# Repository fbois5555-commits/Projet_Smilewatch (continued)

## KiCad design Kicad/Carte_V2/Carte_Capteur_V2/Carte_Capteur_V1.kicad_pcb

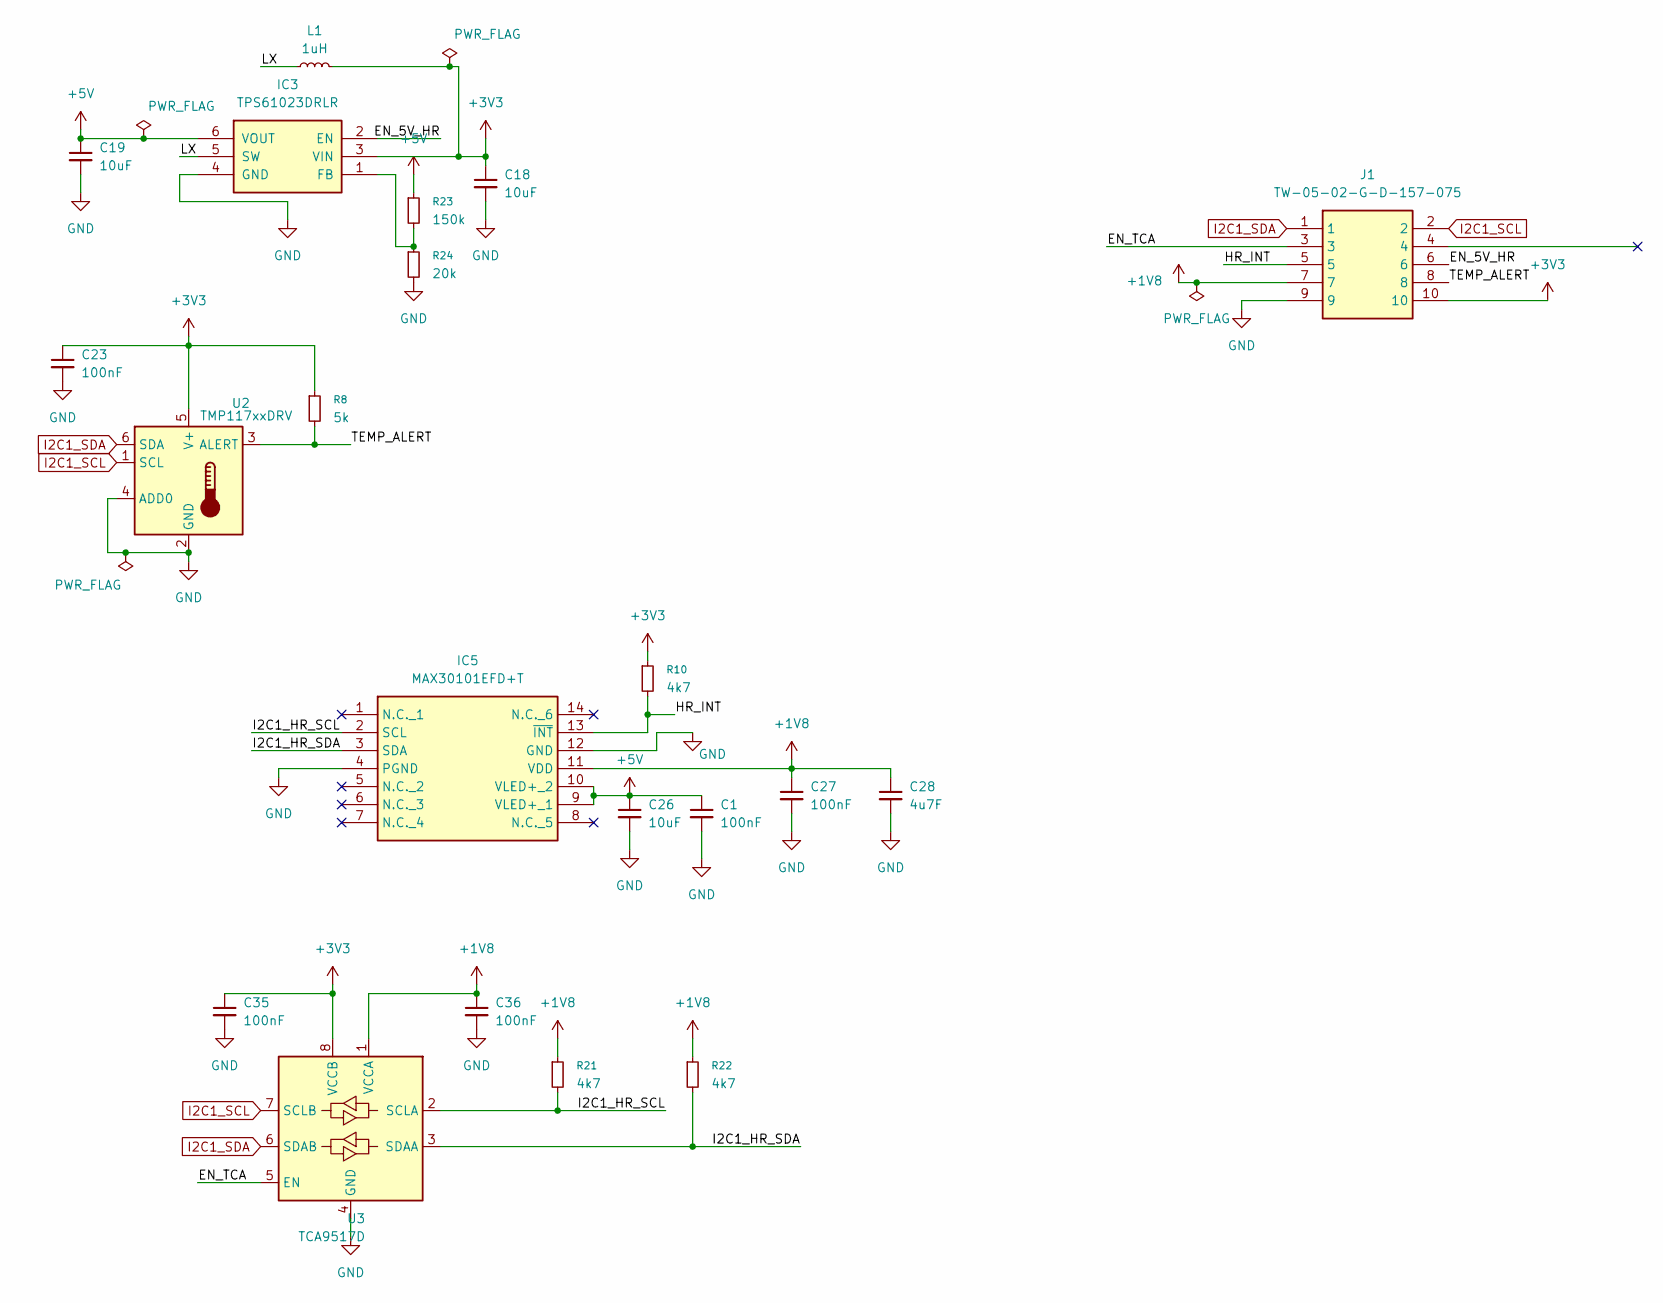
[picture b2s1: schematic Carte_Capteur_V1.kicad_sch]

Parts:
C1, C23, C27, C35, C36: 100nF; C_0402_1005Metric; JLCPCB Part# C1525
C18, C19, C26: 10uF; C_0603_1608Metric; JLCPCB Part# C96446
C28: 4u7F; C_0603_1608Metric; JLCPCB Part# C19666
IC3: TPS61023DRLR; SOT-563; JLCPCB Part# C919459
IC5: MAX30101EFD+T; 14-LEAD-OESIP; Mouser Part Number 700-MAX30101EFD+T
J1: TW-05-02-G-D-157-075; HDRV10W51P200_2X5_1000X400X769P; Mouser Part Number 200-TW0502GD157075
L1: 1uH; L_0603_1608Metric; JLCPCB Part# C882989
R8: 5k; R_0402_1005Metric; JLCPCB Part# C477765
R10, R21, R22: 4k7; R_0402_1005Metric; JLCPCB Part# C25900
R23: 150k; R_0402_1005Metric; JLCPCB Part# C25755
R24: 20k; R_0402_1005Metric; JLCPCB Part# C25765
U2: TMP117xxDRV; WSON-6-1EP_2x2mm_P0.65mm_EP1x1.6mm; JLCPCB Part# C699536
U3: TCA9517D; SOIC-8_3.9x4.9mm_P1.27mm; JLCPCB Part# C182421

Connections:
+1V8: C27.1, C28.1, C36.1, IC5.11 (VDD), J1.7, R21.1, R22.1, U3.1 (VCCA)
+3V3: C18.1, C23.1, C35.1, IC3.3 (VIN), J1.10, L1.2, R8.1, R10.1, U2.5 (V+), U3.8 (VCCB)
+5V: C1.1, C19.1, C26.1, IC3.6 (VOUT), IC5.9 (VLED+_1), IC5.10 (VLED+_2), R23.1
/EN_5V_HR: IC3.2 (EN), J1.6
/EN_TCA: J1.3, U3.5 (EN)
/HR_INT: IC5.13 (~INT), J1.5, R10.2
/I2C1_HR_SCL: IC5.2 (SCL), R21.2, U3.2 (SCLA)
/I2C1_HR_SDA: IC5.3 (SDA), R22.2, U3.3 (SDAA)
/LX: IC3.5 (SW), L1.1
/TEMP_ALERT: J1.8, R8.2, U2.3 (ALERT)
GND: C1.2, C18.2, C19.2, C23.2, C26.2, C27.2, C28.2, C35.2, C36.2, IC3.4 (GND), IC5.4 (PGND), IC5.12 (GND), J1.9, R24.2, U2.2 (GND), U2.4 (ADD0), U3.4 (GND)
I2C1_SCL: J1.2, U2.1 (SCL), U3.7 (SCLB)
I2C1_SDA: J1.1, U2.6 (SDA), U3.6 (SDAB)
unnamed: IC3.1 (FB), R23.2, R24.1

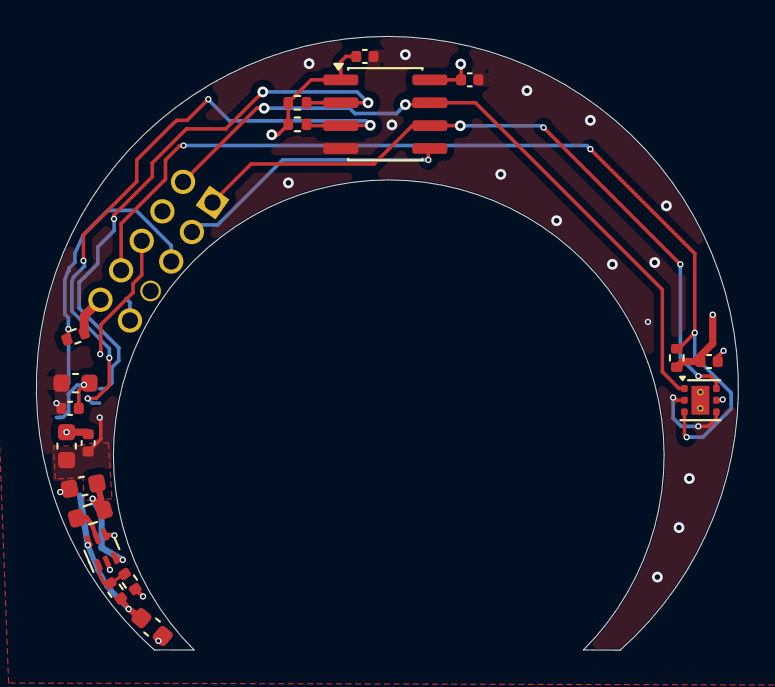
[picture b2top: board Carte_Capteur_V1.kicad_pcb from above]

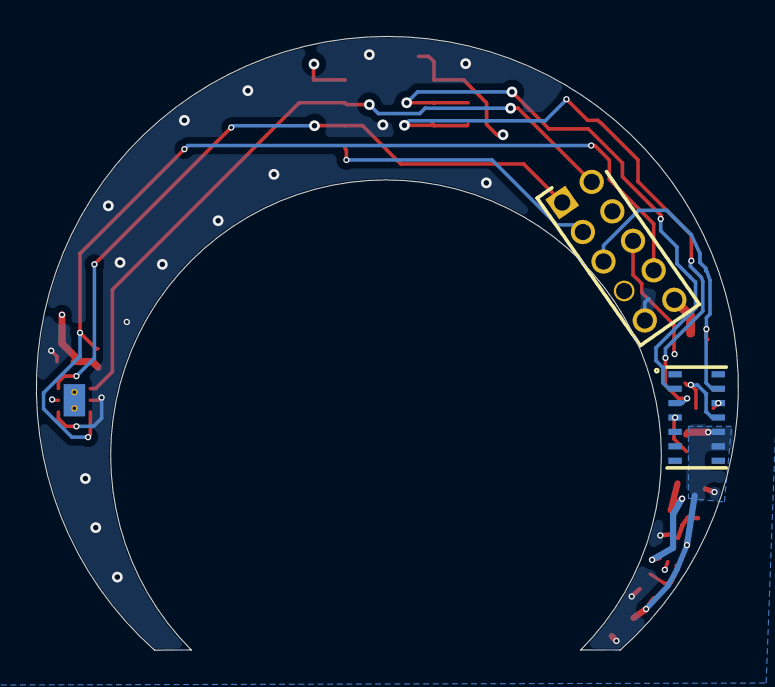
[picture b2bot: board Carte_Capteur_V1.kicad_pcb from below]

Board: 4 copper layers, 39.0 x 34.1 mm, 21 parts (2 on the bottom side), 14 nets.

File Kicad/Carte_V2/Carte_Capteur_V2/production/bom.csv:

Designator,Footprint,Quantity,Value,LCSC Part #
"C1, C23, C27, C35, C36",0402,5,100nF,C1525
"C18, C19, C26",0603,3,10uF,C96446
C28,0603,1,4u7F,C19666
IC3,SOT-563,1,TPS61023DRLR,C919459
IC5,14-LEAD-OESIP,1,MAX30101EFD+T,C2859066
J1,HDRV10W51P200_2X5_1000X400X769P,1,TW-05-02-G-D-157-075,
L1,0603,1,1uH,C882989
"R10, R21, R22",0402,3,4k7,C25900
R23,0402,1,150k,C25755
R24,0402,1,20k,C25765
R8,0402,1,5k,C477765
U2,WSON-6-1EP_2x2mm_P0.65mm_EP1x1.6mm,1,TMP117xxDRV,C699536
U3,SOIC-8_3.9x4.9mm_P1.27mm,1,TCA9517D,C182421

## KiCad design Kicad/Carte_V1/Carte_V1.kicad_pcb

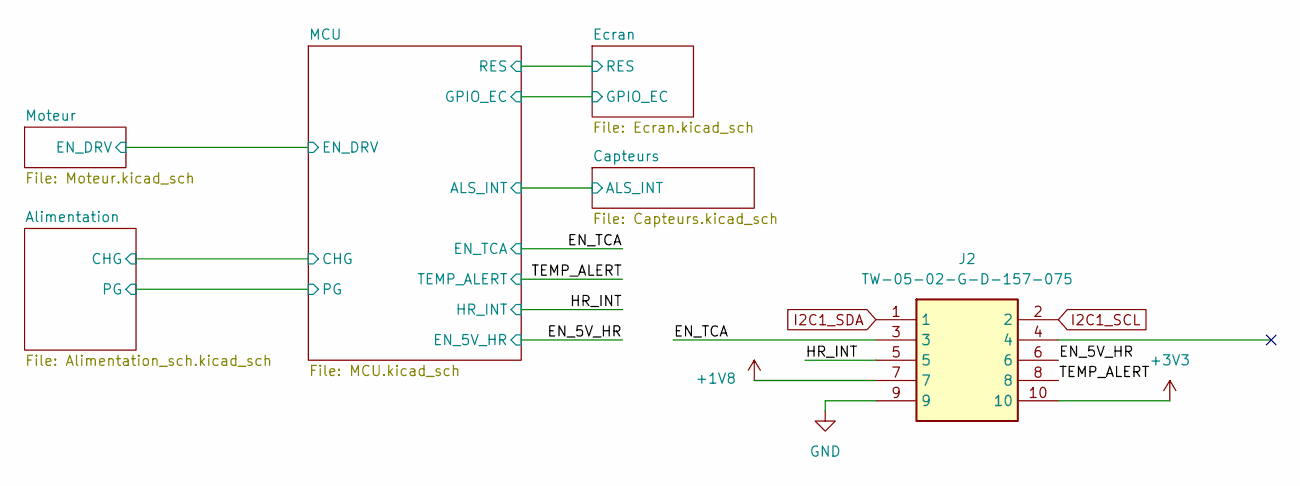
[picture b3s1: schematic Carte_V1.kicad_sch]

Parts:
J2: TW-05-02-G-D-157-075; HDRV10W51P200_2X5_1000X400X769P; Mouser Part Number 200-TW0502GD157075

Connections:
+1V8: J2.7; also elsewhere on the board
+3V3: J2.10; also elsewhere on the board
/EN_5V_HR: J2.6; also elsewhere on the board
/EN_TCA: J2.3; also elsewhere on the board
/HR_INT: J2.5; also elsewhere on the board
/TEMP_ALERT: J2.8; also elsewhere on the board
GND: J2.9; also elsewhere on the board
I2C1_SCL: J2.2; also elsewhere on the board
I2C1_SDA: J2.1; also elsewhere on the board

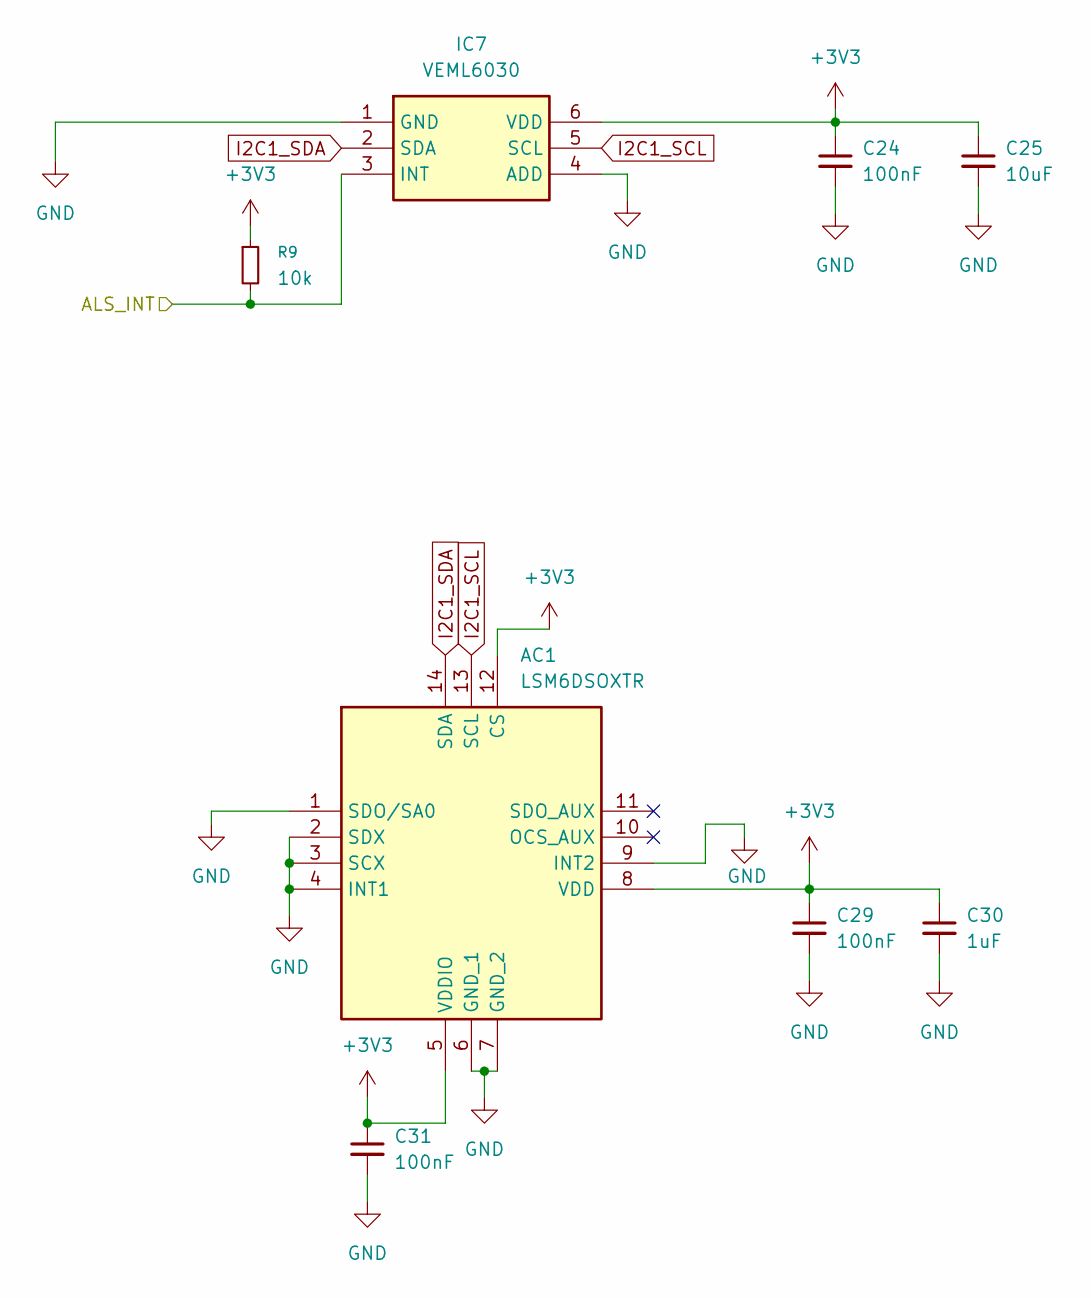
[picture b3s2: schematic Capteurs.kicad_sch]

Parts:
AC1: LSM6DSOXTR; LGA-14_1; Mouser Part Number 511-LSM6DSOXTR
C24, C29, C31: 100nF; C_0402_1005Metric
C25: 10uF; C_0603_1608Metric
C30: 1uF; C_0603_1608Metric
IC7: VEML6030; Mouser Part Number 78-VEML6030
R9: 10k; R_0402_1005Metric

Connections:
+3V3: AC1.5 (VDDIO), AC1.8 (VDD), AC1.12 (CS), C24.1, C25.1, C29.1, C30.1, C31.1, IC7.6 (VDD), R9.1; also elsewhere on the board
/Capteurs/ALS_INT: IC7.3 (INT), R9.2; also elsewhere on the board
GND: AC1.1 (SDO/SA0), AC1.2 (SDX), AC1.3 (SCX), AC1.4 (INT1), AC1.6 (GND_1), AC1.7 (GND_2), AC1.9 (INT2), C24.2, C25.2, C29.2, C30.2, C31.2, IC7.1 (GND), IC7.4 (ADD); also elsewhere on the board
I2C1_SCL: AC1.13 (SCL), IC7.5 (SCL); also elsewhere on the board
I2C1_SDA: AC1.14 (SDA), IC7.2 (SDA); also elsewhere on the board

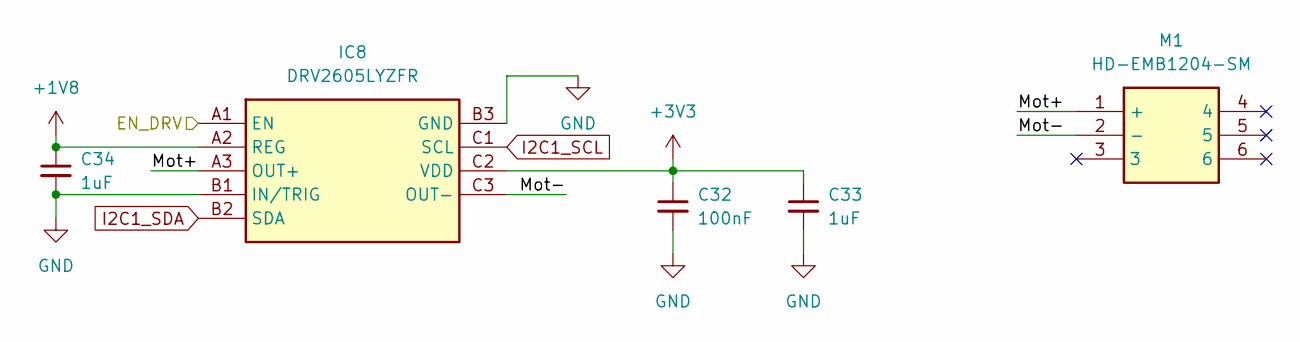
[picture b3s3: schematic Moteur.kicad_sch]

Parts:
C32: 100nF; C_0402_1005Metric
C33, C34: 1uF; C_0603_1608Metric
IC8: DRV2605LYZFR; BGA9C50P3X3_144X144X62; Mouser Part Number 595-DRV2605LYZFR
M1: HD-EMB1204-SM; HDEMB1204SM; Mouser Part Number 665-HD-EMB1204-SM

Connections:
+1V8: C34.1, IC8.A2 (REG); also elsewhere on the board
+3V3: C32.1, C33.1, IC8.C2 (VDD); also elsewhere on the board
/MCU/EN_DRV: IC8.A1 (EN); also elsewhere on the board
/Moteur/Mot+: IC8.A3 (OUT+), M1.1 (+)
/Moteur/Mot-: IC8.C3 (OUT-), M1.2 (-)
GND: C32.2, C33.2, C34.2, IC8.B1 (IN/TRIG), IC8.B3 (GND); also elsewhere on the board
I2C1_SCL: IC8.C1 (SCL); also elsewhere on the board
I2C1_SDA: IC8.B2 (SDA); also elsewhere on the board

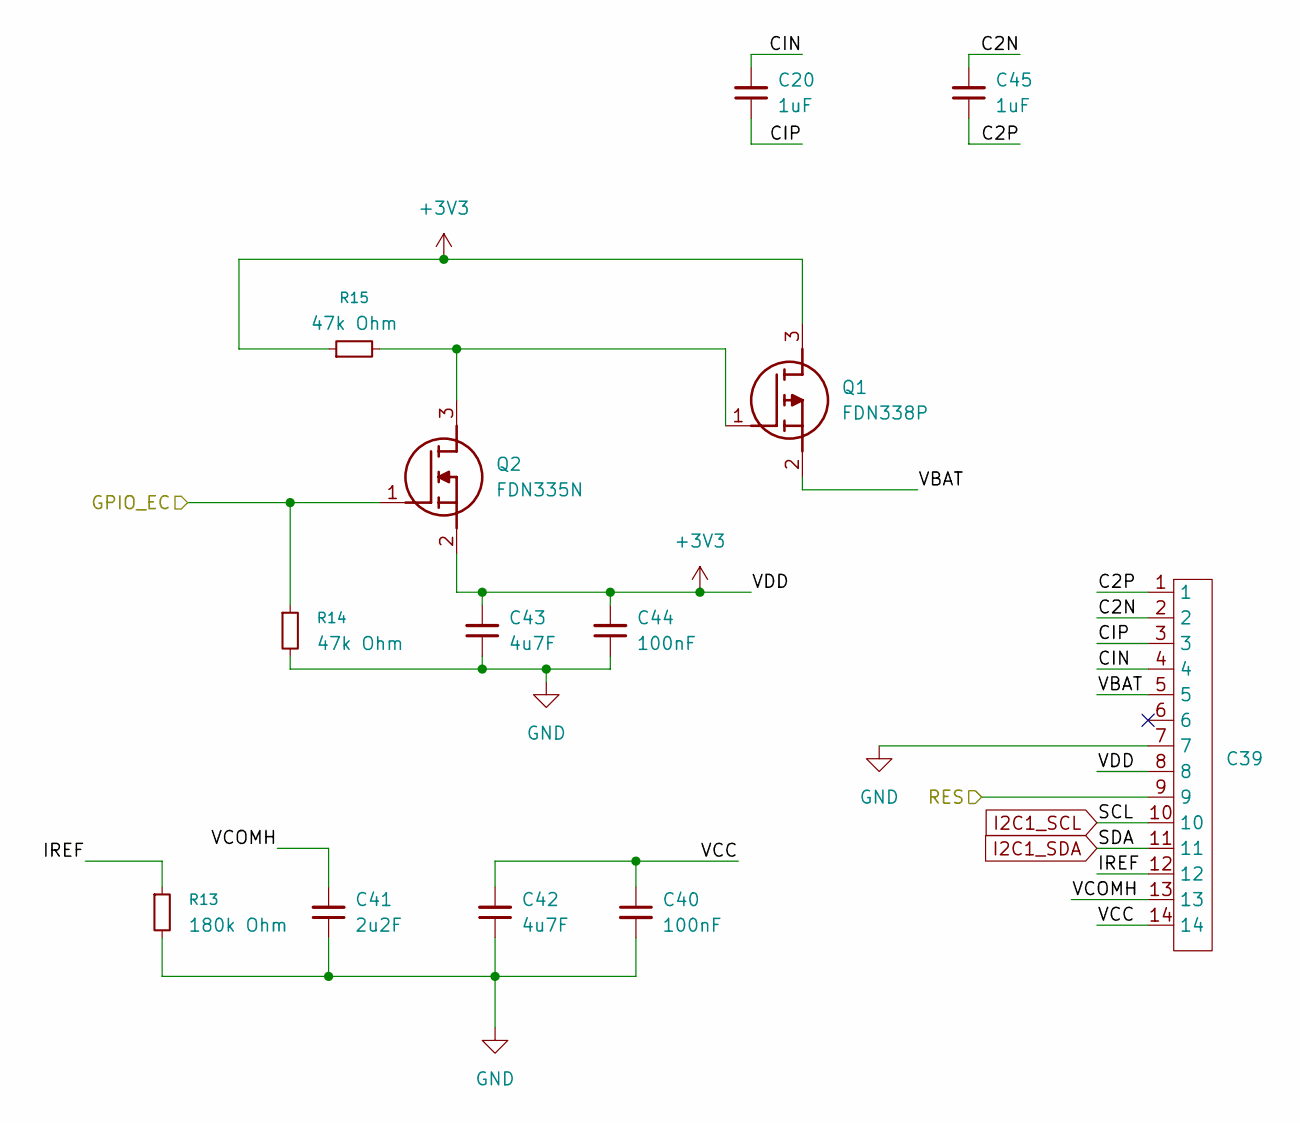
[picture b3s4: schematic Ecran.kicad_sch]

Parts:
C20, C45: 1uF; C_0603_1608Metric
C39: ConnectorMicromatch-14
C40, C44: 100nF; C_0402_1005Metric
C41: 2u2F; C_0603_1608Metric
C42, C43: 4u7F; C_0603_1608Metric
Q1: FDN338P; TSOT-23; Mouser Part Number 512-FDN338P
Q2: FDN335N; TSOT-23; Mouser Part Number 512-FDN335N
R13: 180k Ohm; R_0402_1005Metric
R14, R15: 47k Ohm; R_0402_1005Metric

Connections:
+3V3: C39.8, C43.2, C44.2, Q1.3 (D), Q2.2 (S), R15.1; also elsewhere on the board
/Ecran/C2N: C39.2, C45.2
/Ecran/C2P: C39.1, C45.1
/Ecran/CIN: C20.2, C39.4
/Ecran/CIP: C20.1, C39.3
/Ecran/GPIO_EC: Q2.1 (G), R14.1; also elsewhere on the board
/Ecran/IREF: C39.12, R13.1
/Ecran/RES: C39.9; also elsewhere on the board
/Ecran/VBAT: C39.5, Q1.2 (S)
/Ecran/VCC: C39.14, C40.1, C42.2
/Ecran/VCOMH: C39.13, C41.2
GND: C39.7, C40.2, C41.1, C42.1, C43.1, C44.1, R13.2, R14.2; also elsewhere on the board
I2C1_SCL: C39.10; also elsewhere on the board
I2C1_SDA: C39.11; also elsewhere on the board
unnamed: Q1.1 (G), Q2.3 (D), R15.2

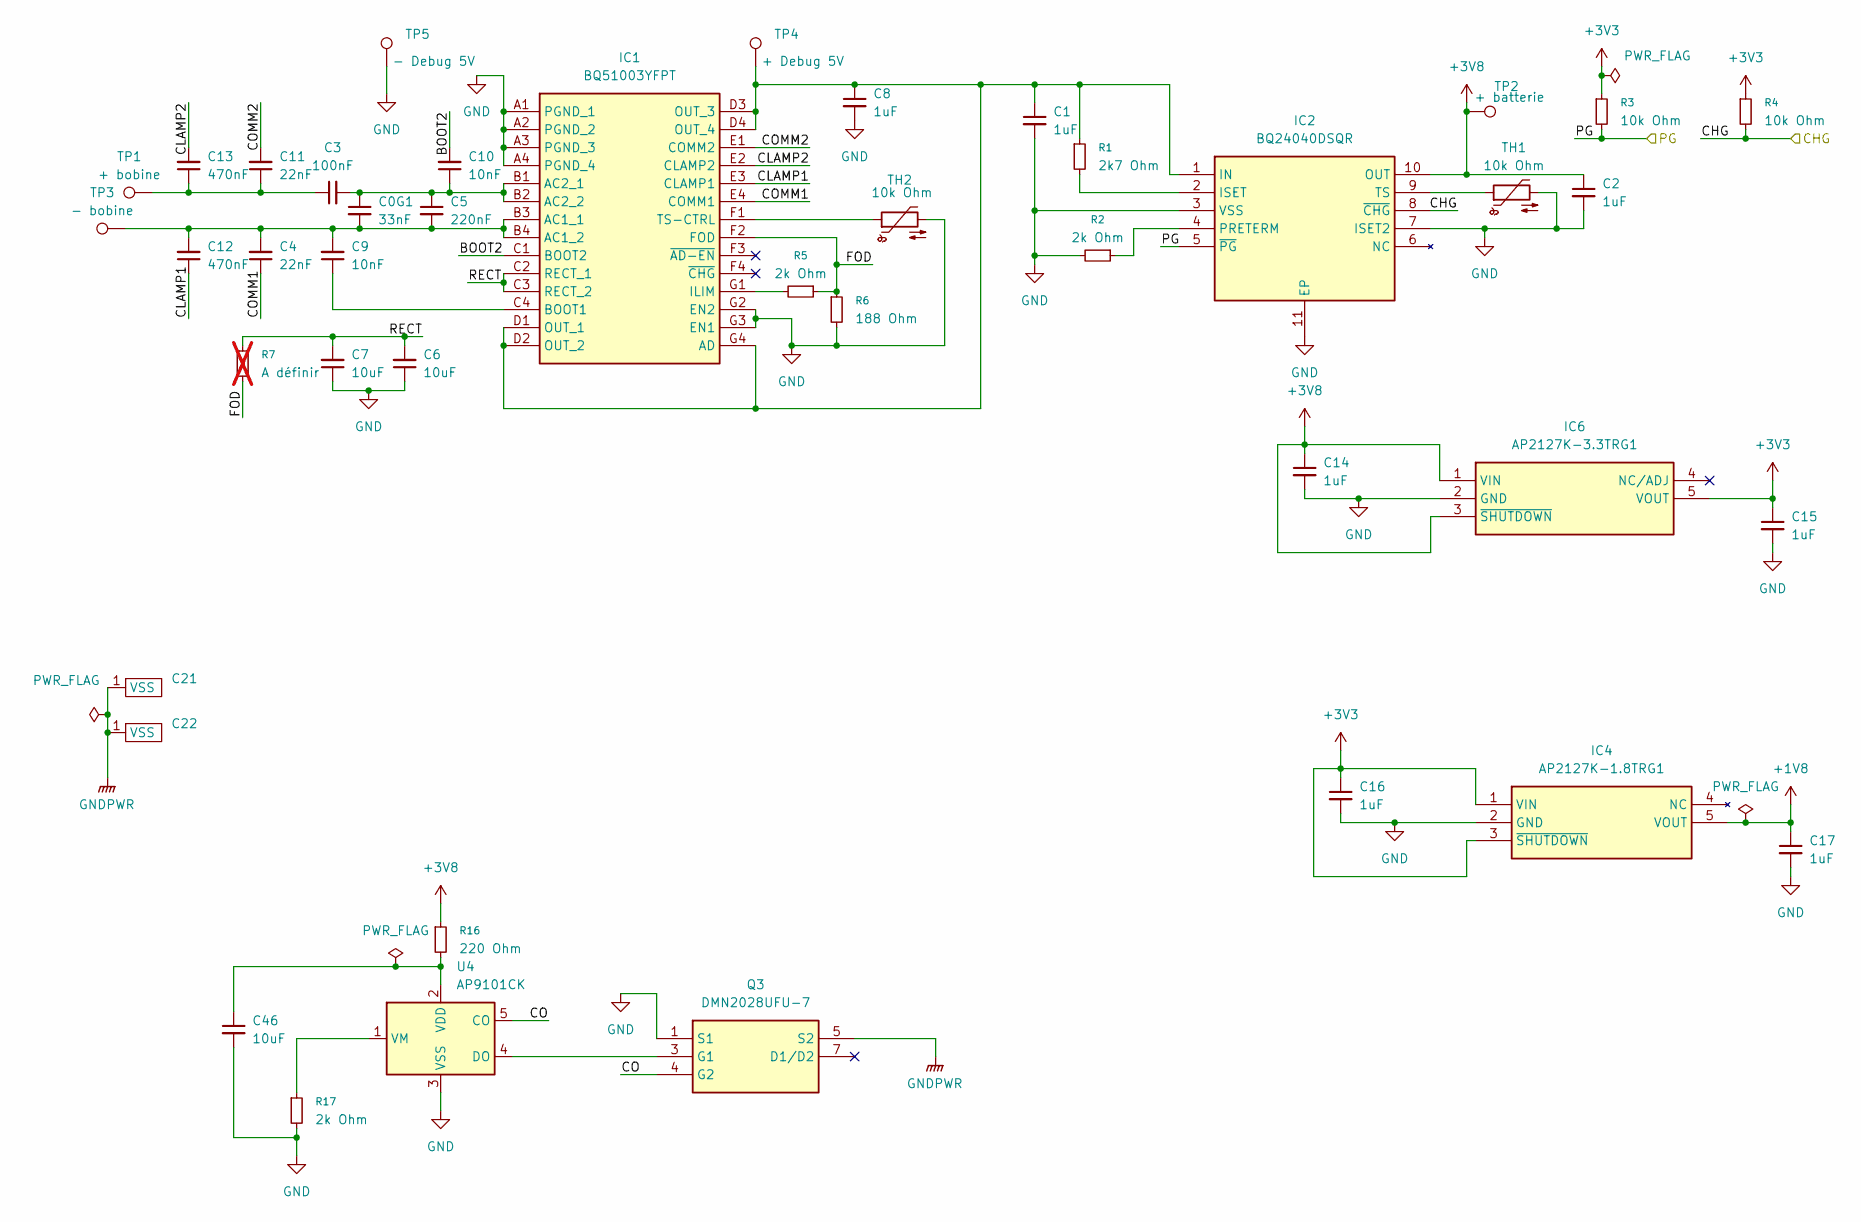
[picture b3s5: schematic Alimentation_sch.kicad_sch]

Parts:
C0G1: 33nF; C_0402_1005Metric
C1, C2, C8, C14, C15, C16, C17: 1uF; C_0603_1608Metric
C3: 100nF; C_0402_1005Metric
C4, C11: 22nF; C_0402_1005Metric
C5: 220nF; C_0402_1005Metric
C6, C7, C46: 10uF; C_0603_1608Metric
C9, C10: 10nF; C_0402_1005Metric
C12, C13: 470nF; C_0402_1005Metric
C21, C22: S1921
IC1: BQ51003YFPT; BGA28C40P4X7_188X301X50; Mouser Part Number 595-BQ51003YFPT
IC2: BQ24040DSQR; WSON-10-1EP_2.5x2.5mm_P0.5mm_EP1.2x2mm_ThermalVias; Mouser Part Number 595-BQ24040DSQR
IC4: AP2127K-1.8TRG1; SOT95P282X145-5N; Mouser Part Number 621-AP2127K-1.8TRG1
IC6: AP2127K-3.3TRG1; SOT95P282X145-5N; Mouser Part Number 621-AP2127K-3.3TRG1
Q3: DMN2028UFU-7; DMN2028UFU7; Mouser Part Number 621-DMN2028UFU-7
R1: 2k7 Ohm; R_0402_1005Metric
R2, R5, R17: 2k Ohm; R_0402_1005Metric
R3, R4: 10k Ohm; R_0402_1005Metric
R6: 188 Ohm; R_0402_1005Metric
R7: A définir; R_0402_1005Metric; not fitted
R16: 220 Ohm; R_0402_1005Metric
TH1, TH2: 10k Ohm; R_0402_1005Metric
TP1: + bobine; TestPoint_Pad_D1.0mm
TP2: + batterie; TestPoint_Pad_D1.0mm
TP3: - bobine; TestPoint_Pad_D1.0mm
TP4: + Debug 5V; TestPoint_Pad_D1.0mm
TP5: - Debug 5V; TestPoint_Pad_1.0x1.0mm
U4: AP9101CK; SOT-23-5

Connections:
+1V8: C17.1, IC4.5 (VOUT); also elsewhere on the board
+3V3: C15.1, C16.1, IC4.1 (VIN), IC4.3 (~SHUTDOWN), IC6.5 (VOUT), R3.1, R4.1; also elsewhere on the board
+3V8: C2.1, C14.1, IC2.10 (OUT), IC6.1 (VIN), IC6.3 (~SHUTDOWN), R16.1, TP2.1
/Alimentation/BOOT2: C10.2, IC1.C1 (BOOT2)
/Alimentation/CHG: IC2.8 (~CHG), R4.2; also elsewhere on the board
/Alimentation/CLAMP1: C12.1, IC1.E3 (CLAMP1)
/Alimentation/CLAMP2: C13.2, IC1.E2 (CLAMP2)
/Alimentation/CO: Q3.4 (G2), U4.5 (CO)
/Alimentation/COMM1: C4.1, IC1.E4 (COMM1)
/Alimentation/COMM2: C11.2, IC1.E1 (COMM2)
/Alimentation/FOD: IC1.F2 (FOD), R5.1, R6.1, R7.2
/Alimentation/PG: IC2.5 (~PG), R3.2; also elsewhere on the board
/Alimentation/RECT: C6.2, C7.2, IC1.C2 (RECT_1), IC1.C3 (RECT_2), R7.1
GND: C1.2, C2.2, C6.1, C7.1, C8.2, C14.2, C15.2, C16.2, C17.2, C46.2, IC1.A1 (PGND_1), IC1.A2 (PGND_2), IC1.A3 (PGND_3), IC1.A4 (PGND_4), IC1.G2 (EN2), IC1.G3 (EN1), IC2.3 (VSS), IC2.7 (ISET2), IC2.11 (EP), IC4.2 (GND), IC6.2 (GND), Q3.1 (S1), R2.2, R6.2, R17.2, TH1.2, TH2.2, TP5.1, U4.3 (VSS); also elsewhere on the board
GNDPWR: C21.1 (VSS), C22.1 (VSS), Q3.5 (S2)
unnamed: C3.1, C11.1, C13.1, TP1.1
unnamed: C0G1.2, C4.2, C5.2, C9.2, C12.2, IC1.B3 (AC1_1), IC1.B4 (AC1_2), TP3.1
unnamed: C0G1.1, C3.2, C5.1, C10.1, IC1.B1 (AC2_1), IC1.B2 (AC2_2)
unnamed: C1.1, C8.1, IC1.D1 (OUT_1), IC1.D2 (OUT_2), IC1.D3 (OUT_3), IC1.D4 (OUT_4), IC1.G4 (AD), IC2.1 (IN), R1.1, TP4.1
unnamed: C9.1, IC1.C4 (BOOT1)
unnamed: IC1.G1 (ILIM), R5.2
unnamed: IC1.F1 (TS-CTRL), TH2.1
unnamed: IC2.2 (ISET), R1.2
unnamed: IC2.4 (PRETERM), R2.1
unnamed: IC2.9 (TS), TH1.1
unnamed: Q3.3 (G1), U4.4 (DO)
unnamed: C46.1, R16.2, U4.2 (VDD)
unnamed: R17.1, U4.1 (VM)

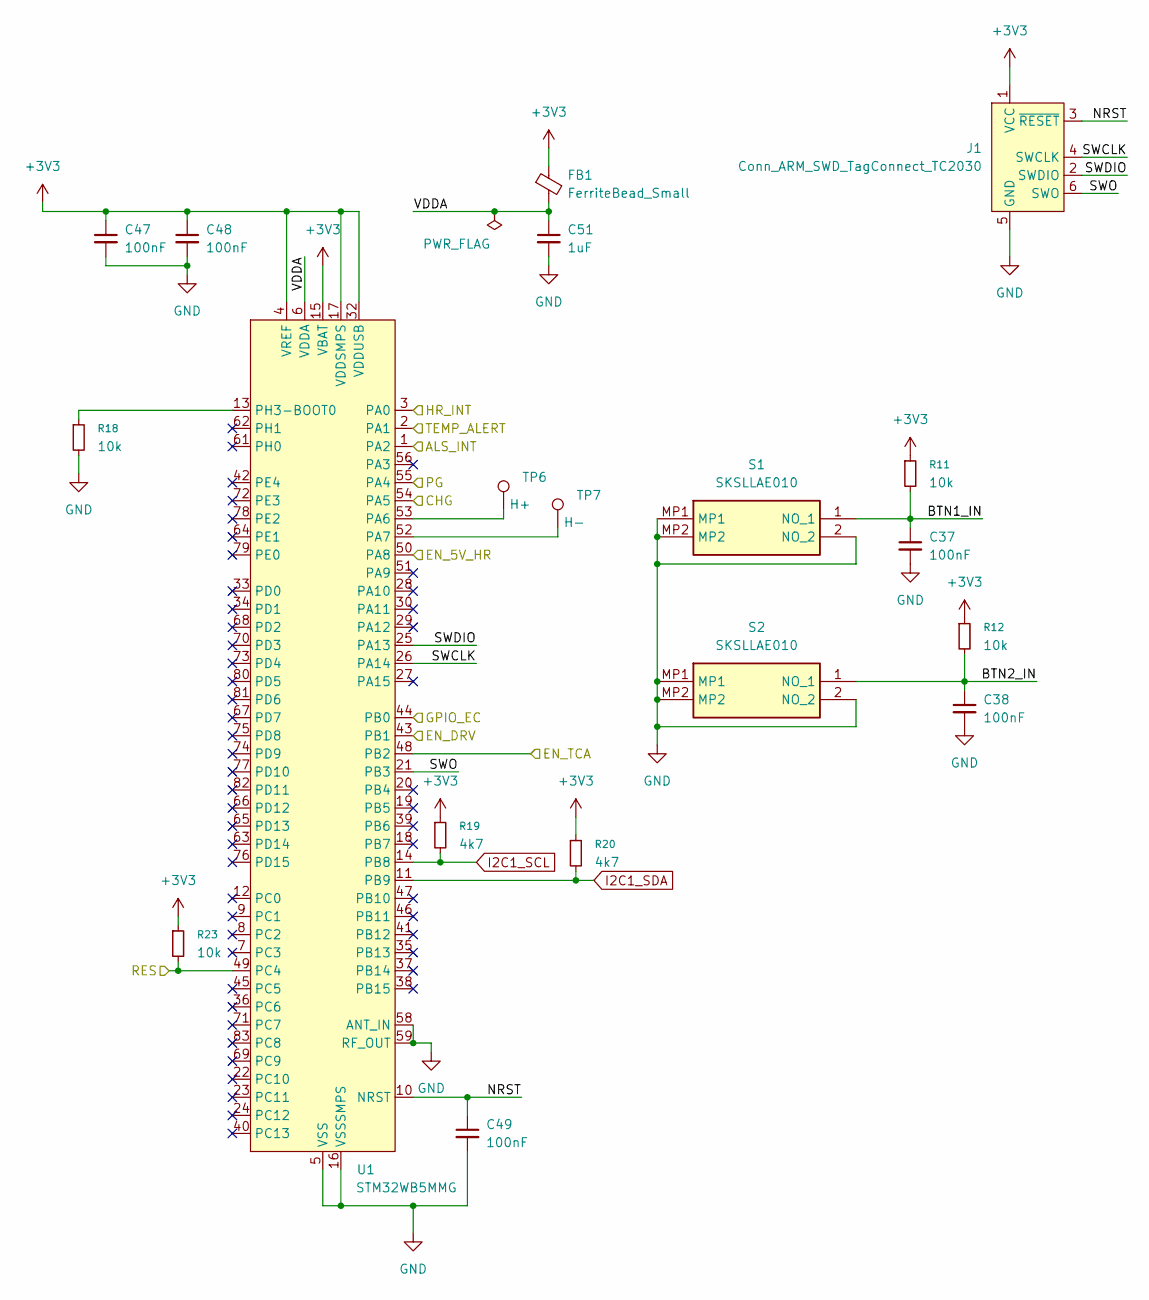
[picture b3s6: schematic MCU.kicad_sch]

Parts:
C37, C38, C47, C48, C49: 100nF; C_0402_1005Metric
C51: 1uF; C_0603_1608Metric
FB1: FerriteBead_Small; L_0603_1608Metric
J1: Conn_ARM_SWD_TagConnect_TC2030; Tag-Connect_TC2030-IDC-NL_2x03_P1.27mm_Vertical
R11, R12, R18, R23: 10k; R_0402_1005Metric
R19, R20: 4k7; R_0402_1005Metric
S1, S2: SKSLLAE010; Mouser Part Number 688-SKSLLAE010
TP6: H+; TestPoint_Pad_D1.0mm
TP7: H-; TestPoint_Pad_D1.0mm
U1: STM32WB5MMG; ST-SiP-LGA-86-11x7.3mm

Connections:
+3V3: C47.1, C48.1, FB1.1, J1.1 (VCC), R11.1, R12.1, R19.1, R20.1, R23.1, U1.4 (VREF), U1.15 (VBAT), U1.17 (VDDSMPS), U1.32 (VDDUSB); also elsewhere on the board
/Alimentation/CHG: U1.54 (PA5); also elsewhere on the board
/Alimentation/PG: U1.55 (PA4); also elsewhere on the board
/Capteurs/ALS_INT: U1.1 (PA2); also elsewhere on the board
/EN_5V_HR: U1.50 (PA8); also elsewhere on the board
/EN_TCA: U1.48 (PB2); also elsewhere on the board
/Ecran/GPIO_EC: U1.44 (PB0); also elsewhere on the board
/Ecran/RES: R23.2, U1.49 (PC4); also elsewhere on the board
/HR_INT: U1.3 (PA0); also elsewhere on the board
/MCU/BTN1_IN: C37.1, R11.2, S1.1 (NO_1)
/MCU/BTN2_IN: C38.1, R12.2, S2.1 (NO_1)
/MCU/EN_DRV: U1.43 (PB1); also elsewhere on the board
/MCU/NRST: C49.1, J1.3 (~RESET), U1.10 (NRST)
/MCU/SWCLK: J1.4 (SWCLK), U1.26 (PA14)
/MCU/SWDIO: J1.2 (SWDIO), U1.25 (PA13)
/MCU/SWO: J1.6 (SWO), U1.21 (PB3)
/MCU/VDDA: C51.1, FB1.2, U1.6 (VDDA)
/TEMP_ALERT: U1.2 (PA1); also elsewhere on the board
GND: C37.2, C38.2, C47.2, C48.2, C49.2, C51.2, J1.5 (GND), R18.2, S1.2 (NO_2), S1.MP1, S1.MP2, S2.2 (NO_2), S2.MP1, S2.MP2, U1.5 (VSS), U1.16 (VSSSMPS), U1.31 (VSS), U1.57 (VSS), U1.58 (ANT_IN), U1.59 (RF_OUT), U1.60 (VSS), U1.84 (VSS), U1.86 (VSS); also elsewhere on the board
I2C1_SCL: R19.2, U1.14 (PB8); also elsewhere on the board
I2C1_SDA: R20.2, U1.11 (PB9); also elsewhere on the board
unnamed: TP6.1, U1.53 (PA6)
unnamed: TP7.1, U1.52 (PA7)
unnamed: R18.1, U1.13 (PH3-BOOT0)

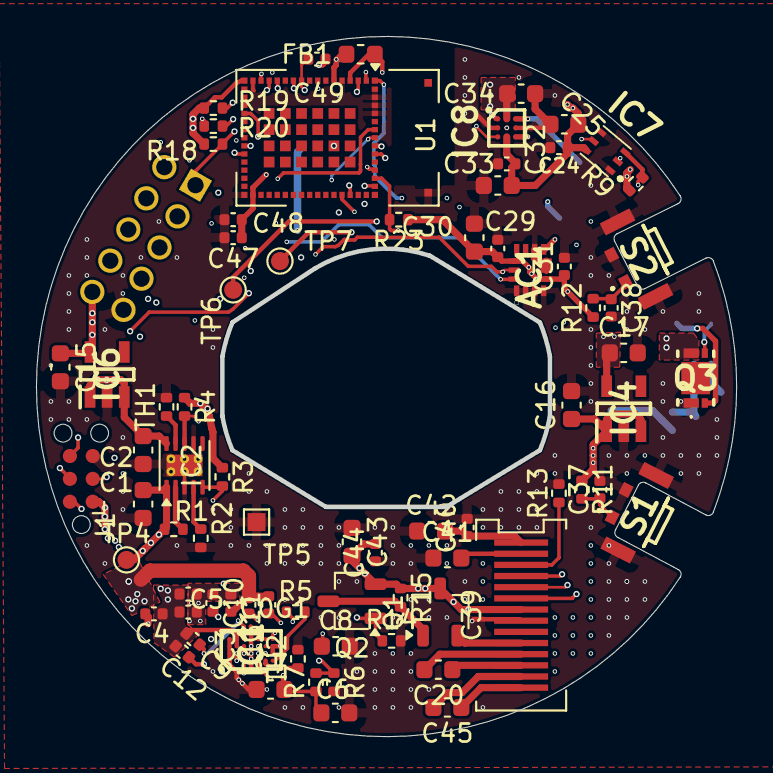
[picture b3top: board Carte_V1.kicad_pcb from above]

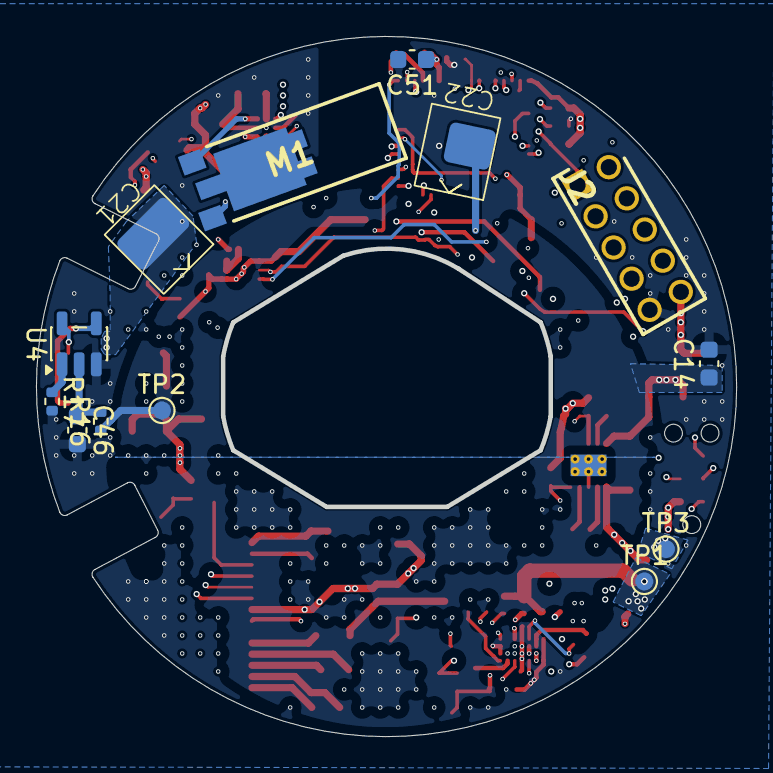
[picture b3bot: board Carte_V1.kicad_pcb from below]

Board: 6 copper layers, 38.9 x 38.9 mm, 89 parts (13 on the bottom side), 59 nets.

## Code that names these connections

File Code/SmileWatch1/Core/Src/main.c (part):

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  HAL_GPIO_WritePin(GPIOB, MIYOTA_HM_Pin | OLED_RES_Pin | HR_5V_EN_Pin, GPIO_PIN_RESET);
  HAL_GPIO_WritePin(GPIOD, OLED_PWR_EN_Pin, GPIO_PIN_RESET);

  /* Outputs on GPIOA: PA7 (Miyota H+), PA1 (DRV_EN), PA4 (TCA_EN) */
  GPIO_InitStruct.Pin   = MIYOTA_HP_Pin | DRV_EN_Pin | TCA_EN_Pin;
  GPIO_InitStruct.Mode  = GPIO_MODE_OUTPUT_PP;
  GPIO_InitStruct.Pull  = GPIO_NOPULL;
  GPIO_InitStruct.Speed = GPIO_SPEED_FREQ_LOW;
  HAL_GPIO_Init(GPIOA, &GPIO_InitStruct);

  /* Outputs on GPIOB: PB5 (Miyota H-), PB4 (OLED RES), PB0 (+5V_HR Boost EN) */
  GPIO_InitStruct.Pin   = MIYOTA_HM_Pin | OLED_RES_Pin | HR_5V_EN_Pin;
  GPIO_InitStruct.Mode  = GPIO_MODE_OUTPUT_PP;
  GPIO_InitStruct.Pull  = GPIO_NOPULL;
  GPIO_InitStruct.Speed = GPIO_SPEED_FREQ_LOW;
  HAL_GPIO_Init(GPIOB, &GPIO_InitStruct);

  /* Output on GPIOD: PD7 (OLED Power Switch GPIO_EC) */
  GPIO_InitStruct.Pin   = OLED_PWR_EN_Pin;
  GPIO_InitStruct.Mode  = GPIO_MODE_OUTPUT_PP;
  GPIO_InitStruct.Pull  = GPIO_NOPULL;
  GPIO_InitStruct.Speed = GPIO_SPEED_FREQ_LOW;
  HAL_GPIO_Init(GPIOD, &GPIO_InitStruct);

  /* Push-button inputs on GPIOC: PC5 (2h Top S2) & PC4 (4h Bottom S1) */
  GPIO_InitStruct.Pin   = BTN_TOP_2H_Pin | BTN_BOT_4H_Pin;
  GPIO_InitStruct.Mode  = GPIO_MODE_INPUT;
  GPIO_InitStruct.Pull  = GPIO_PULLUP;
  HAL_GPIO_Init(GPIOC, &GPIO_InitStruct);

  /* Sensor interrupts on GPIOA: TEMP_ALERT (PA9), IMU_INTSA (PA10), IMU_INTPA (PA15), ALS_INT (PA12) */
  GPIO_InitStruct.Pin   = TEMP_ALERT_Pin | IMU_INTSA_Pin | IMU_INTPA_Pin | ALS_INT_Pin;
  GPIO_InitStruct.Mode  = GPIO_MODE_INPUT;
  GPIO_InitStruct.Pull  = GPIO_PULLUP;
  HAL_GPIO_Init(GPIOA, &GPIO_InitStruct);

  /* HR interrupt (PB6) & BQ24040 ~CHG status (PB2, active low) on GPIOB */
  GPIO_InitStruct.Pin   = HR_INT_Pin | BQ_CHG_Pin;
  GPIO_InitStruct.Mode  = GPIO_MODE_INPUT;
  GPIO_InitStruct.Pull  = GPIO_PULLUP;
  HAL_GPIO_Init(GPIOB, &GPIO_InitStruct);
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
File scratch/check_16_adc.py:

import re

with open('Kicad/Carte_V2/Carte_V2.kicad_pcb', 'r', encoding='utf-8') as f:
    pcb = f.read()

# All 16 ADC pins:
adc_list = [
    ('F8', 'PC0', 'ADC1_IN1'),
    ('G8', 'PC1', 'ADC1_IN2'),
    ('G9', 'PC2', 'ADC1_IN3'),
    ('G10', 'PC3', 'ADC1_IN4'),
    ('G7', 'PA0', 'ADC1_IN5'),
    ('G6', 'PA1', 'ADC1_IN6'),
    ('F6', 'PA2', 'ADC1_IN7'),
    ('J8', 'PA3', 'ADC1_IN8'),
    ('K10', 'PA4', 'ADC1_IN9'),
    ('K9', 'PA5', 'ADC1_IN10'),
    ('H7', 'PA6', 'ADC1_IN11'),
    ('H6', 'PA7', 'ADC1_IN12'),
    ('G4', 'PC4', 'ADC1_IN13'),
    ('H5', 'PC5', 'ADC1_IN14'),
    ('J7', 'PA8', 'ADC1_IN15'),
    ('K8', 'PA9', 'ADC1_IN16')
]

for pnum, pname, adc_ch in adc_list:
    m = re.search(r'\(pad\s+\"' + pnum + r'\"[\s\S]*?\(at\s+([\d\.-]+)\s+([\d\.-]+)[\s\S]*?\(net\s+\"([^\"]+)\"\)', pcb)
    if m:
        dx, dy, net = float(m.group(1)), float(m.group(2)), m.group(3)
        ax = round(104.6025 - dx, 4)
        ay = round(68.3825 - dy, 4)
        print(f"{pnum:4} ({pname:5}, {adc_ch:10}) at ({ax:8.4f}, {ay:8.4f}) -> net={net}")

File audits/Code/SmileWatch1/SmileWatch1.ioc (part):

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Mcu.Name=STM32WB5MMGHx
Mcu.Package=LGA86
Mcu.UserName=STM32WB5MMGHx
PB8.Mode=I2C
PB8.Signal=I2C1_SCL
PB9.Mode=I2C
PB9.Signal=I2C1_SDA
RCC.HSE_VALUE=32000000
board=custom

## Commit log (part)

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2026-04-05 Début 3D
2026-04-07 Update kicad
2026-04-11 Update datasheet
2026-04-12 presque tt les composants sauf méca et bouton
2026-04-15 Validation mouser
2026-04-18 debut kicad
2026-04-21 update kicad et 3D
2026-04-21 fin schéma
2026-04-25 update 3D (presque fini)
2026-04-25 update 3D
2026-04-27 Fin première phase 3D
2026-04-29 routage pcb
2026-06-29 Début de releccture
